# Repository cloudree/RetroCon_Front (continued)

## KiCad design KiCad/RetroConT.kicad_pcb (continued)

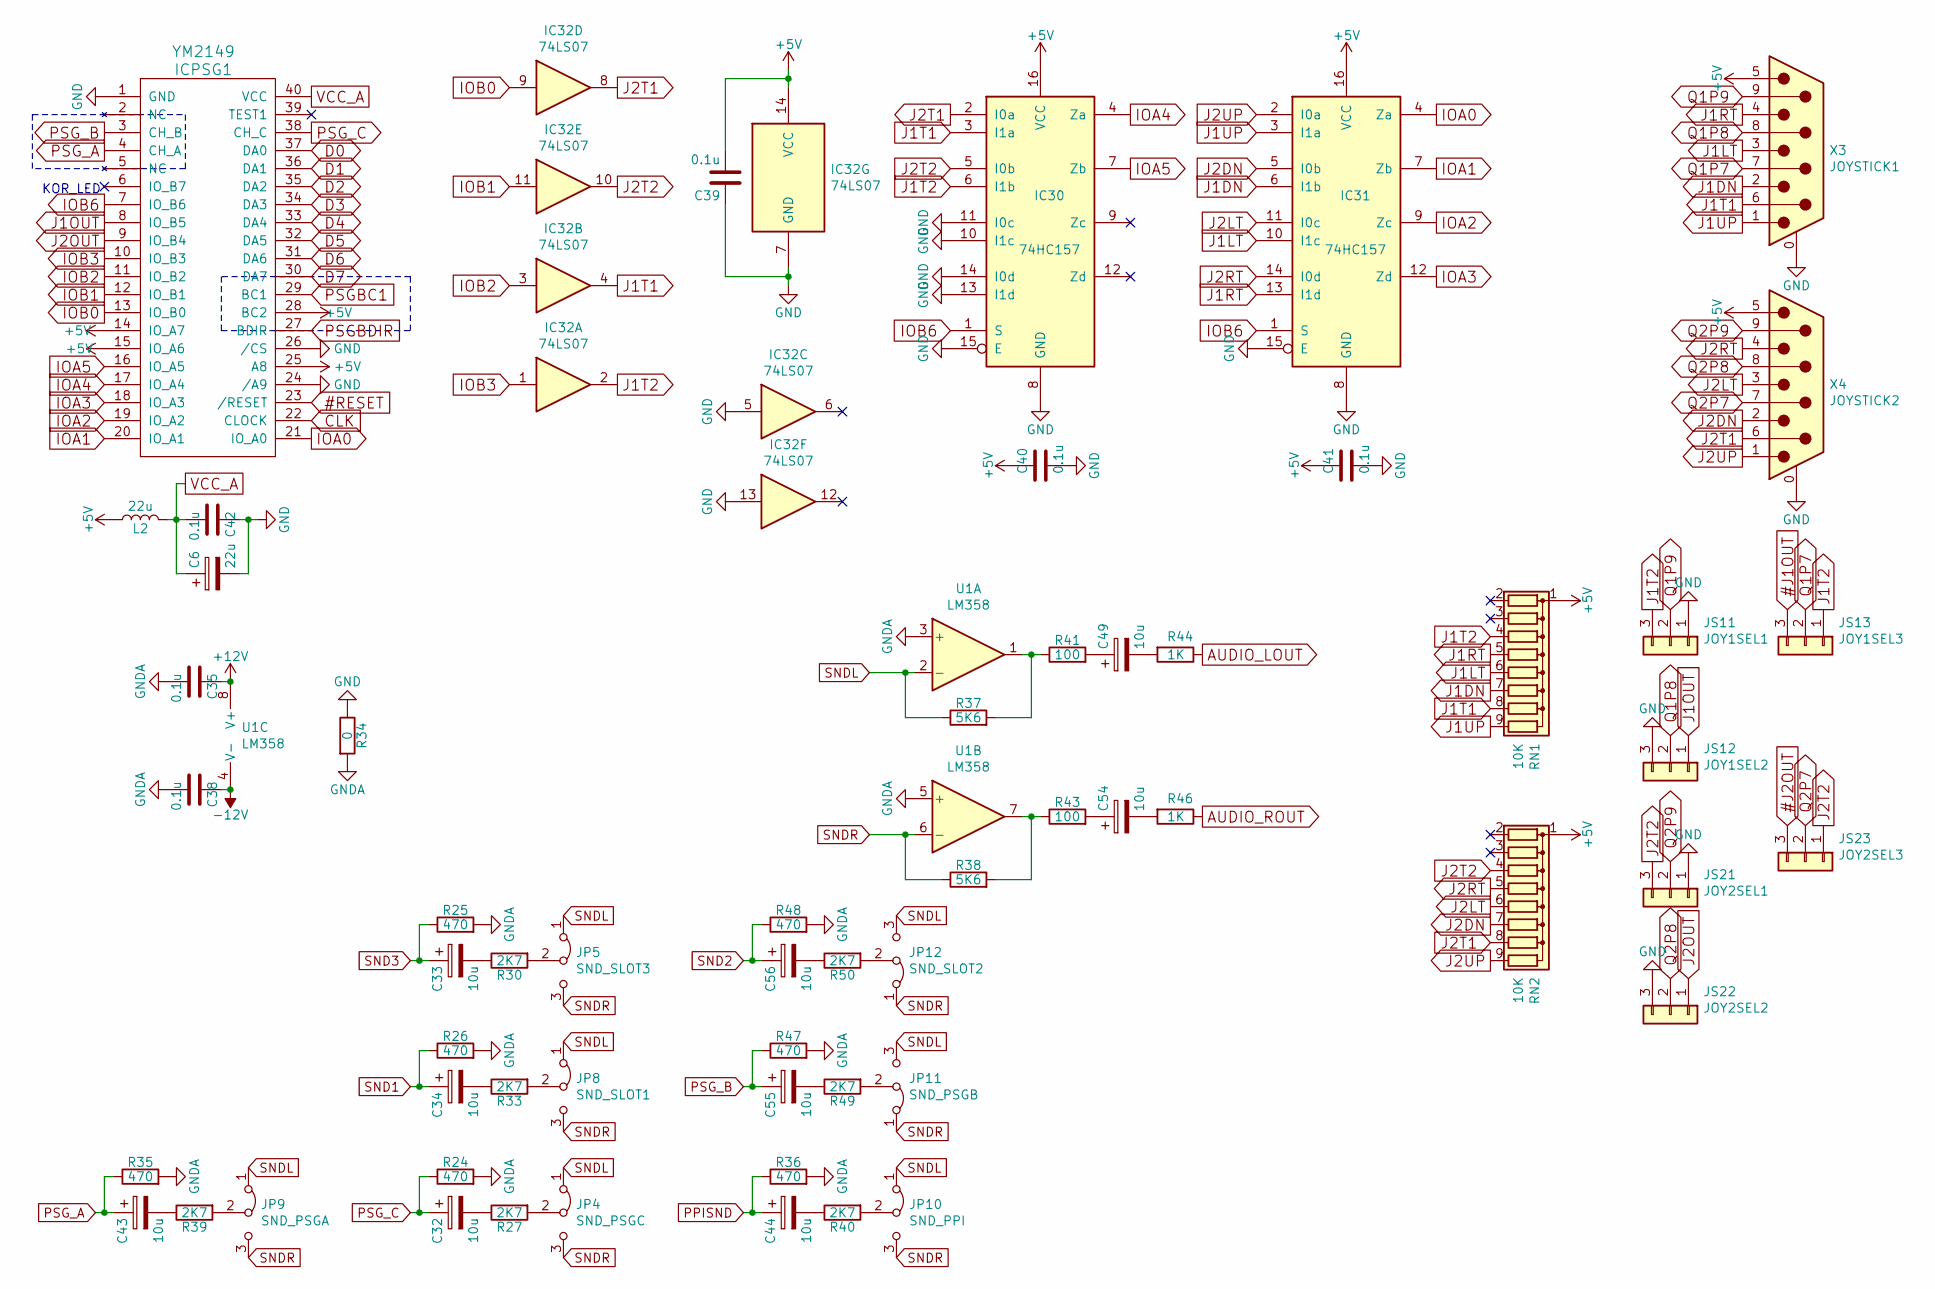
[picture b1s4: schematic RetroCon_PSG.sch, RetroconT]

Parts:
C6: 22u; CP_Radial_D6.3mm_P2.50mm
C32, C33, C34, C43, C44, C49, C54, C55, C56: 10u; CP_Radial_D6.3mm_P2.50mm
C35, C38, C39, C40, C41, C42: 0.1u; C_0805_2012Metric_Pad1.15x1.40mm_HandSolder
IC30, IC31: 74HC157; SOIC-16_3.9x9.9mm_P1.27mm
IC32: 74LS07; SOIC-14_3.9x8.7mm_P1.27mm
ICPSG1: YM2149; DIP-40_W15.24mm_Socket
JP4: SND_PSGC; SolderJumper-3_P1.3mm_Bridged12_RoundedPad1.0x1.5mm_NumberL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
JP5: SND_SLOT3; SolderJumper-3_P1.3mm_Bridged12_RoundedPad1.0x1.5mm_NumberL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
JP8: SND_SLOT1; SolderJumper-3_P1.3mm_Bridged12_RoundedPad1.0x1.5mm_NumberL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
JP9: SND_PSGA; SolderJumper-3_P1.3mm_Bridged12_RoundedPad1.0x1.5mm_NumberL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
JP10: SND_PPI; SolderJumper-3_P1.3mm_Bridged12_RoundedPad1.0x1.5mm_NumberL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
JP11: SND_PSGB; SolderJumper-3_P1.3mm_Bridged12_RoundedPad1.0x1.5mm_NumberL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
JP12: SND_SLOT2; SolderJumper-3_P1.3mm_Bridged12_RoundedPad1.0x1.5mm_NumberL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
JS11: JOY1SEL1; PinSocket_1x03_P2.54mm_Vertical
JS12: JOY1SEL2; PinSocket_1x03_P2.54mm_Vertical
JS13: JOY1SEL3; PinSocket_1x03_P2.54mm_Vertical
JS21: JOY2SEL1; PinSocket_1x03_P2.54mm_Vertical
JS22: JOY2SEL2; PinSocket_1x03_P2.54mm_Vertical
JS23: JOY2SEL3; PinSocket_1x03_P2.54mm_Vertical
L2: 22u; L_0805_2012Metric_Pad1.15x1.40mm_HandSolder
R24, R25, R26, R35, R36, R47, R48: 470; R_0805_HandSoldering
R27, R30, R33, R39, R40, R49, R50: 2K7; R_0805_HandSoldering
R34: 0; R_0805_HandSoldering
R37, R38: 5K6; R_0805_HandSoldering
R41, R43: 100; R_0805_HandSoldering
R44, R46: 1K; R_0805_HandSoldering
RN1, RN2: 10K; R_Array_SIP9
U1: LM358; DIP-8_W7.62mm_Socket
X3: JOYSTICK1; DSUB-9_Male_Horizontal_P2.77x2.84mm_EdgePinOffset4.94mm_Hou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
X4: JOYSTICK2; DSUB-9_Male_Horizontal_P2.77x2.84mm_EdgePinOffset4.94mm_Hou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

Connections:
#ExRESET: ICPSG1.23 (/RESET); also elsewhere on the board
#J1OUT: JS13.3; also elsewhere on the board
#J2OUT: JS23.3; also elsewhere on the board
+5V: C39.2, C40.1, C41.1, IC30.16 (VCC), IC31.16 (VCC), IC32.14 (VCC), ICPSG1.14 (IO_A7), ICPSG1.15 (IO_A6), ICPSG1.25 (A8), ICPSG1.28 (BC2), L2.1, RN1.1 (common), RN2.1 (common), X3.5, X4.5; also elsewhere on the board
+12V: C35.1, U1.8 (V+); also elsewhere on the board
-12V: C38.1, U1.4 (V-); also elsewhere on the board
AUDIO_LOUT: R44.1; also elsewhere on the board
AUDIO_ROUT: R46.1; also elsewhere on the board
CLK: ICPSG1.22 (CLOCK); also elsewhere on the board
D0: ICPSG1.37 (DA0); also elsewhere on the board
D1: ICPSG1.36 (DA1); also elsewhere on the board
D2: ICPSG1.35 (DA2); also elsewhere on the board
D3: ICPSG1.34 (DA3); also elsewhere on the board
D4: ICPSG1.33 (DA4); also elsewhere on the board
D5: ICPSG1.32 (DA5); also elsewhere on the board
D6: ICPSG1.31 (DA6); also elsewhere on the board
D7: ICPSG1.30 (DA7); also elsewhere on the board
GND: C6.2, C39.1, C40.2, C41.2, C42.1, IC30.8 (GND), IC30.10 (I1c), IC30.11 (I0c), IC30.13 (I1d), IC30.14 (I0d), IC30.15 (E), IC31.8 (GND), IC31.15 (E), IC32.5, IC32.7 (GND), IC32.13, ICPSG1.1 (GND), ICPSG1.24 (/A9), ICPSG1.26 (/CS), JS11.1, JS12.3, JS21.1, JS22.3, R34.1, X3.0 (PAD), X4.0 (PAD); also elsewhere on the board
GNDA: C35.2, C38.2, R24.2, R25.2, R26.2, R34.2, R35.2, R36.2, R47.2, R48.2, U1.3 (+), U1.5 (+); also elsewhere on the board
IOA0: IC31.4 (Za), ICPSG1.21 (IO_A0)
IOA1: IC31.7 (Zb), ICPSG1.20 (IO_A1)
IOA2: IC31.9 (Zc), ICPSG1.19 (IO_A2)
IOA3: IC31.12 (Zd), ICPSG1.18 (IO_A3)
IOA4: IC30.4 (Za), ICPSG1.17 (IO_A4)
IOA5: IC30.7 (Zb), ICPSG1.16 (IO_A5)
IOB0: IC32.9, ICPSG1.13 (IO_B0)
IOB1: IC32.11, ICPSG1.12 (IO_B1)
IOB2: IC32.3, ICPSG1.11 (IO_B2)
IOB3: IC32.1, ICPSG1.10 (IO_B3)
IOB6: IC30.1 (S), IC31.1 (S), ICPSG1.7 (IO_B6)
J1DN: IC31.6 (I1b), RN1.7 (R6), X3.2
J1LT: IC31.10 (I1c), RN1.6 (R5), X3.3
J1OUT: ICPSG1.8 (IO_B5), JS12.1; also elsewhere on the board
J1RT: IC31.13 (I1d), RN1.5 (R4), X3.4
J1T1: IC30.3 (I1a), IC32.4, RN1.8 (R7), X3.6
J1T2: IC30.6 (I1b), IC32.2, JS11.3, JS13.1, RN1.4 (R3)
J1UP: IC31.3 (I1a), RN1.9 (R8), X3.1
J2DN: IC31.5 (I0b), RN2.7 (R6), X4.2
J2LT: IC31.11 (I0c), RN2.6 (R5), X4.3
J2OUT: ICPSG1.9 (IO_B4), JS22.1; also elsewhere on the board
J2RT: IC31.14 (I0d), RN2.5 (R4), X4.4
J2T1: IC30.2 (I0a), IC32.8, RN2.8 (R7), X4.6
J2T2: IC30.5 (I0b), IC32.10, JS21.3, JS23.1, RN2.4 (R3)
J2UP: IC31.2 (I0a), RN2.9 (R8), X4.1
unnamed: C32.2, R27.1
unnamed: C33.2, R30.1
unnamed: C34.2, R33.1
unnamed: C43.2, R39.1
unnamed: C44.2, R40.1
unnamed: C49.1, R41.2
unnamed: C49.2, R44.2
unnamed: C54.1, R43.2
unnamed: C54.2, R46.2
unnamed: C55.2, R49.1
unnamed: C56.2, R50.1
unnamed: JP4.2 (C), R27.2
unnamed: JP5.2 (C), R30.2
unnamed: JP8.2 (C), R33.2
unnamed: JP9.2 (C), R39.2
unnamed: JP10.2 (C), R40.2
unnamed: JP11.2 (C), R49.2
unnamed: JP12.2 (C), R50.2
unnamed: R37.2, R41.1, U1.1
unnamed: R38.2, R43.1, U1.7
PPISND: C44.1, R36.1; also elsewhere on the board
PSGBC1: ICPSG1.29 (BC1); also elsewhere on the board
PSGBDIR: ICPSG1.27 (BDIR); also elsewhere on the board
PSG_A: C43.1, ICPSG1.4 (CH_A), R35.1
PSG_B: C55.1, ICPSG1.3 (CH_B), R47.1
PSG_C: C32.1, ICPSG1.38 (CH_C), R24.1
Q1P7: JS13.2, X3.7
Q1P8: JS12.2, X3.8
Q1P9: JS11.2, X3.9
Q2P7: JS23.2, X4.7
Q2P8: JS22.2, X4.8
Q2P9: JS21.2, X4.9
SND1: C34.1, R26.1; also elsewhere on the board
SND2: C56.1, R48.1; also elsewhere on the board
SND3: C33.1, R25.1; also elsewhere on the board
SNDL: JP4.1 (A), JP5.1 (A), JP8.1 (A), JP9.1 (A), JP10.1 (A), JP11.3 (B), JP12.3 (B), R37.1, U1.2 (-)
SNDR: JP4.3 (B), JP5.3 (B), JP8.3 (B), JP9.3 (B), JP10.3 (B), JP11.1 (A), JP12.1 (A), R38.1, U1.6 (-)
VCC_A: C6.1, C42.2, ICPSG1.40 (VCC), L2.2

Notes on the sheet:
KOR_LED

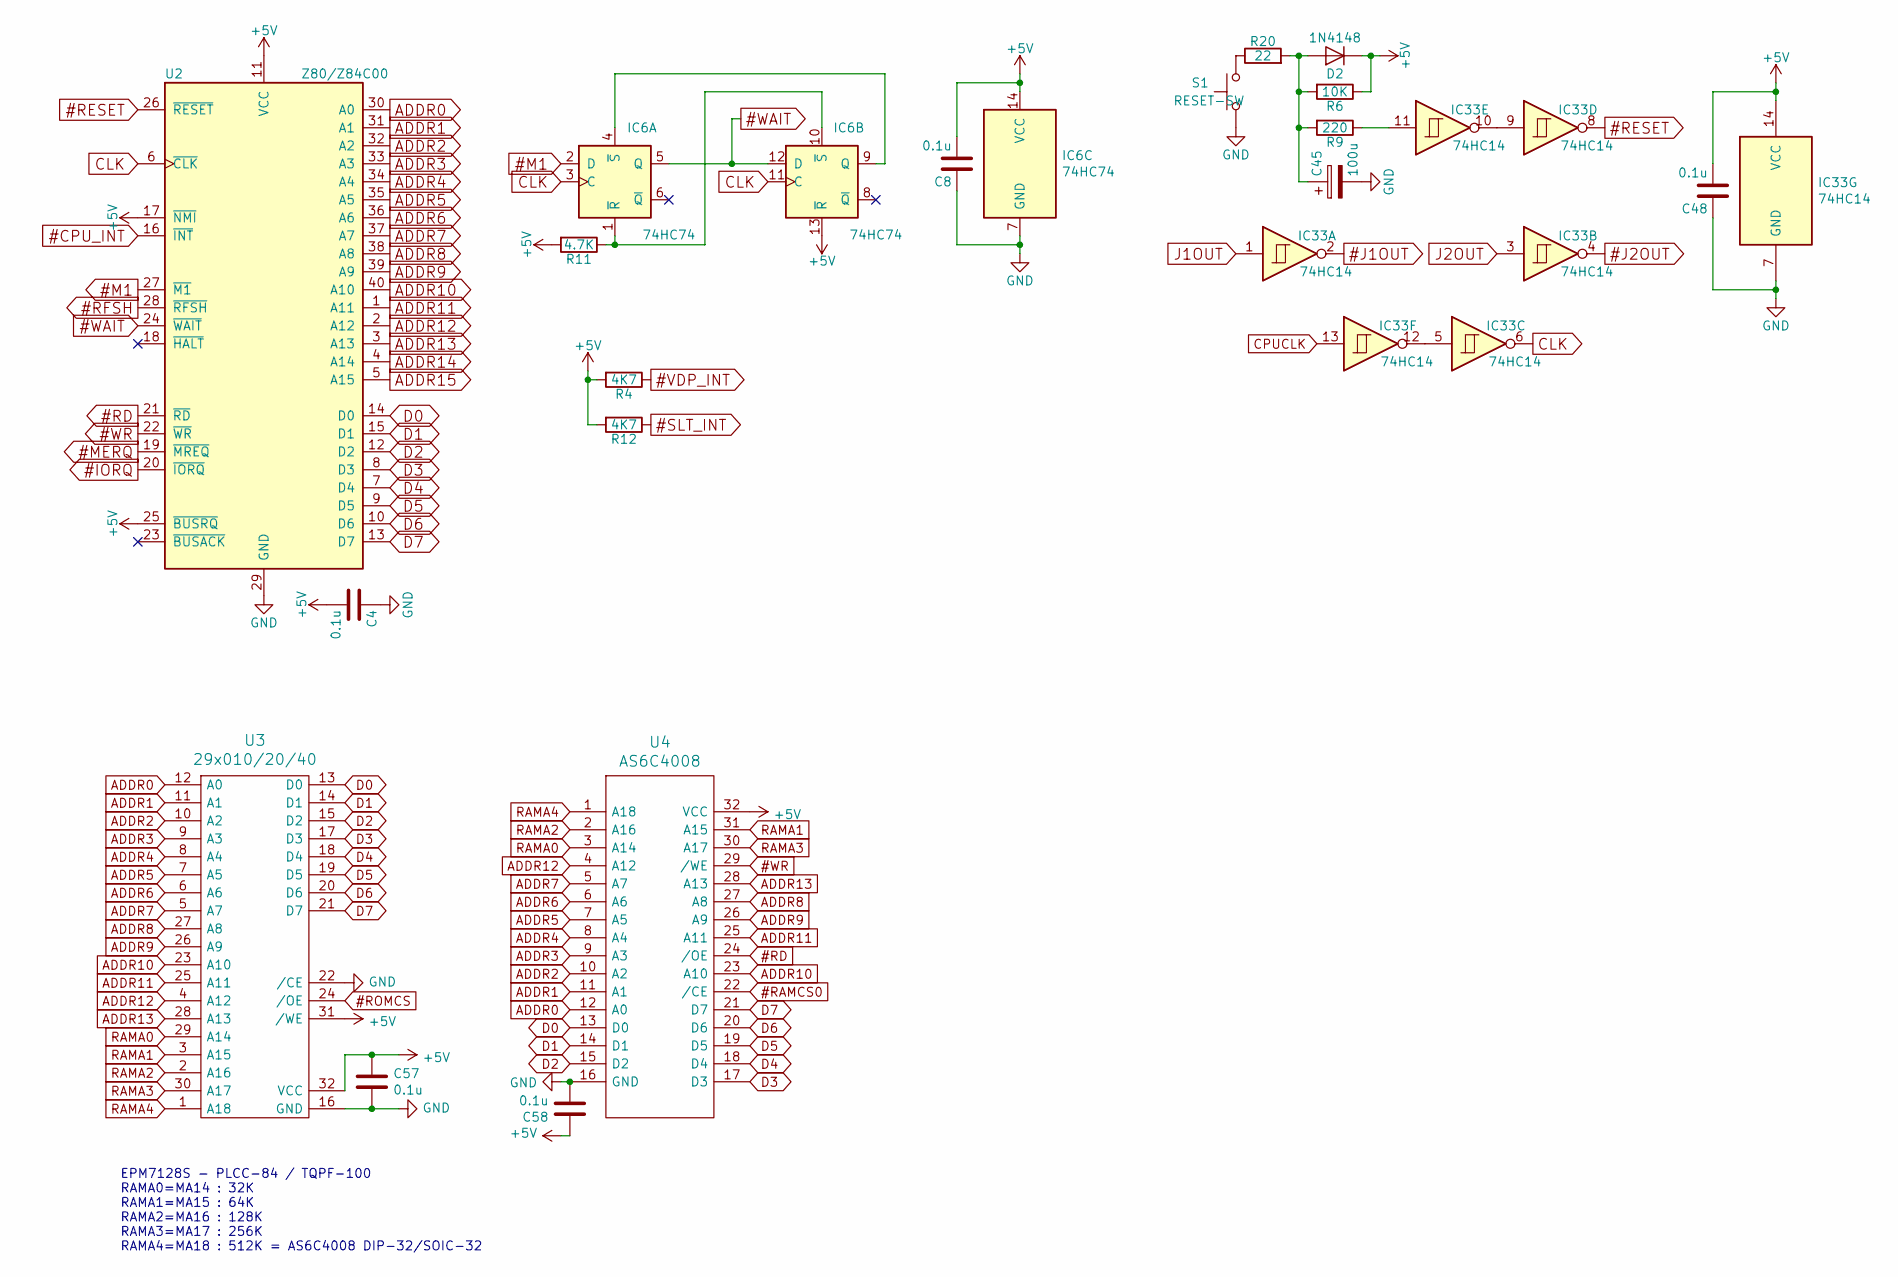
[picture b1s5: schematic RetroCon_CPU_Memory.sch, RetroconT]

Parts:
C4, C8, C48, C57, C58: 0.1u; C_0805_2012Metric_Pad1.15x1.40mm_HandSolder
C45: 100u; CP_Radial_D6.3mm_P2.50mm
D2: 1N4148; D_0805_2012Metric_Pad1.15x1.40mm_HandSolder
IC6: 74HC74; SOIC-14_3.9x8.7mm_P1.27mm
IC33: 74HC14; SOIC-14_3.9x8.7mm_P1.27mm
R4, R12: 4K7; R_0805_HandSoldering
R6: 10K; R_0805_HandSoldering
R9: 220; R_0805_HandSoldering
R11: 4.7K; R_0805_HandSoldering
R20: 22; R_0805_HandSoldering
S1: RESET-SW; Tact_Switch_Long_Angle
U2: Z80/Z84C00; DIP-40_W15.24mm_Socket
U3: 29x010/20/40; DIP-32_W15.24mm_Socket
U4: AS6C4008; DIP-32_W15.24mm_Socket

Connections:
#CPU_INT: U2.16 (~INT~); also elsewhere on the board
#ExIORQ: U2.20 (~IORQ~); also elsewhere on the board
#ExM1: IC6.2 (D), U2.27 (~M1~); also elsewhere on the board
#ExMERQ: U2.19 (~MREQ~); also elsewhere on the board
#ExRD: U2.21 (~RD~), U4.24 (/OE); also elsewhere on the board
#ExRESET: IC33.8, U2.26 (~RESET~); also elsewhere on the board
#ExRFSH: U2.28 (~RFSH~); also elsewhere on the board
#ExWAIT: IC6.5 (Q), IC6.12 (D), U2.24 (~WAIT~); also elsewhere on the board
#ExWR: U2.22 (~WR~), U4.29 (/WE); also elsewhere on the board
#J1OUT: IC33.2; also elsewhere on the board
#J2OUT: IC33.4; also elsewhere on the board
#RAMCS0: U4.22 (/CE); also elsewhere on the board
#ROMCS: U3.24 (/OE); also elsewhere on the board
#SLT_INT: R12.1; also elsewhere on the board
#VDP_INT: R4.1; also elsewhere on the board
+5V: C4.2, C8.2, C48.2, C57.1, C58.1, D2.1 (K), IC6.13 (~R), IC6.14 (VCC), IC33.14 (VCC), R4.2, R6.1, R11.2, R12.2, U2.11 (VCC), U2.17 (~NMI~), U2.25 (~BUSRQ~), U3.31 (/WE), U3.32 (VCC), U4.32 (VCC); also elsewhere on the board
ADDR0: U2.30 (A0), U3.12 (A0), U4.12 (A0); also elsewhere on the board
ADDR1: U2.31 (A1), U3.11 (A1), U4.11 (A1); also elsewhere on the board
ADDR2: U2.32 (A2), U3.10 (A2), U4.10 (A2); also elsewhere on the board
ADDR3: U2.33 (A3), U3.9 (A3), U4.9 (A3); also elsewhere on the board
ADDR4: U2.34 (A4), U3.8 (A4), U4.8 (A4); also elsewhere on the board
ADDR5: U2.35 (A5), U3.7 (A5), U4.7 (A5); also elsewhere on the board
ADDR6: U2.36 (A6), U3.6 (A6), U4.6 (A6); also elsewhere on the board
ADDR7: U2.37 (A7), U3.5 (A7), U4.5 (A7); also elsewhere on the board
ADDR8: U2.38 (A8), U3.27 (A8), U4.27 (A8); also elsewhere on the board
ADDR9: U2.39 (A9), U3.26 (A9), U4.26 (A9); also elsewhere on the board
ADDR10: U2.40 (A10), U3.23 (A10), U4.23 (A10); also elsewhere on the board
ADDR11: U2.1 (A11), U3.25 (A11), U4.25 (A11); also elsewhere on the board
ADDR12: U2.2 (A12), U3.4 (A12), U4.4 (A12); also elsewhere on the board
ADDR13: U2.3 (A13), U3.28 (A13), U4.28 (A13); also elsewhere on the board
ADDR14: U2.4 (A14); also elsewhere on the board
ADDR15: U2.5 (A15); also elsewhere on the board
CLK: IC6.3 (C), IC6.11 (C), IC33.6, U2.6 (~CLK~); also elsewhere on the board
CPUCLK: IC33.13; also elsewhere on the board
D0: U2.14 (D0), U3.13 (D0), U4.13 (D0); also elsewhere on the board
D1: U2.15 (D1), U3.14 (D1), U4.14 (D1); also elsewhere on the board
D2: U2.12 (D2), U3.15 (D2), U4.15 (D2); also elsewhere on the board
D3: U2.8 (D3), U3.17 (D3), U4.17 (D3); also elsewhere on the board
D4: U2.7 (D4), U3.18 (D4), U4.18 (D4); also elsewhere on the board
D5: U2.9 (D5), U3.19 (D5), U4.19 (D5); also elsewhere on the board
D6: U2.10 (D6), U3.20 (D6), U4.20 (D6); also elsewhere on the board
D7: U2.13 (D7), U3.21 (D7), U4.21 (D7); also elsewhere on the board
GND: C4.1, C8.1, C45.2, C48.1, C57.2, C58.2, IC6.7 (GND), IC33.7 (GND), S1.1, U2.29 (GND), U3.16 (GND), U3.22 (/CE), U4.16 (GND); also elsewhere on the board
J1OUT: IC33.1; also elsewhere on the board
J2OUT: IC33.3; also elsewhere on the board
unnamed: C45.1, D2.2 (A), R6.2, R9.2, R20.2
unnamed: IC6.1 (~R), IC6.10 (~S), R11.1
unnamed: IC6.4 (~S), IC6.9 (Q)
unnamed: IC33.9, IC33.10
unnamed: IC33.11, R9.1
unnamed: IC33.5, IC33.12
unnamed: R20.1, S1.2
RAMA0: U3.29 (A14), U4.3 (A14); also elsewhere on the board
RAMA1: U3.3 (A15), U4.31 (A15); also elsewhere on the board
RAMA2: U3.2 (A16), U4.2 (A16); also elsewhere on the board
RAMA3: U3.30 (A17), U4.30 (A17); also elsewhere on the board
RAMA4: U3.1 (A18), U4.1 (A18); also elsewhere on the board

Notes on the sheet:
EPM7128S - PLCC-84 / TQPF-100 RAMA0=MA14 : 32K RAMA1=MA15 : 64K RAMA2=MA16 : 128K RAMA3=MA17 : 256K RAMA4=MA18 : 512K = AS6C4008 DIP-32/SOIC-32

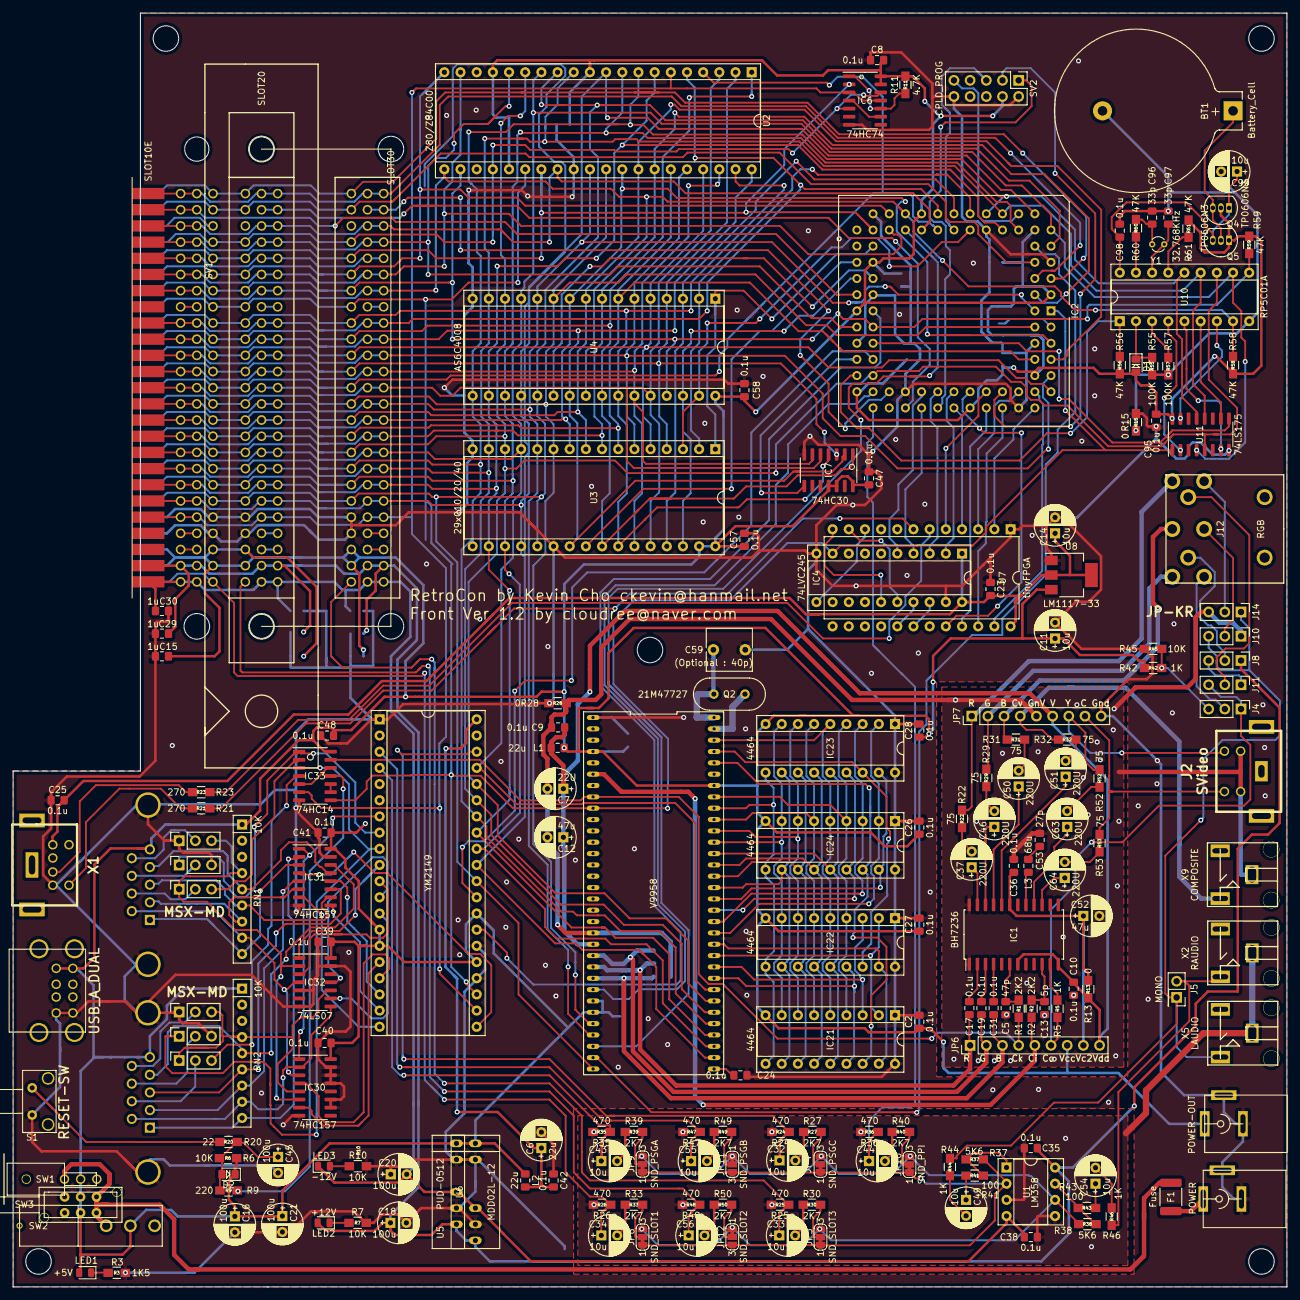
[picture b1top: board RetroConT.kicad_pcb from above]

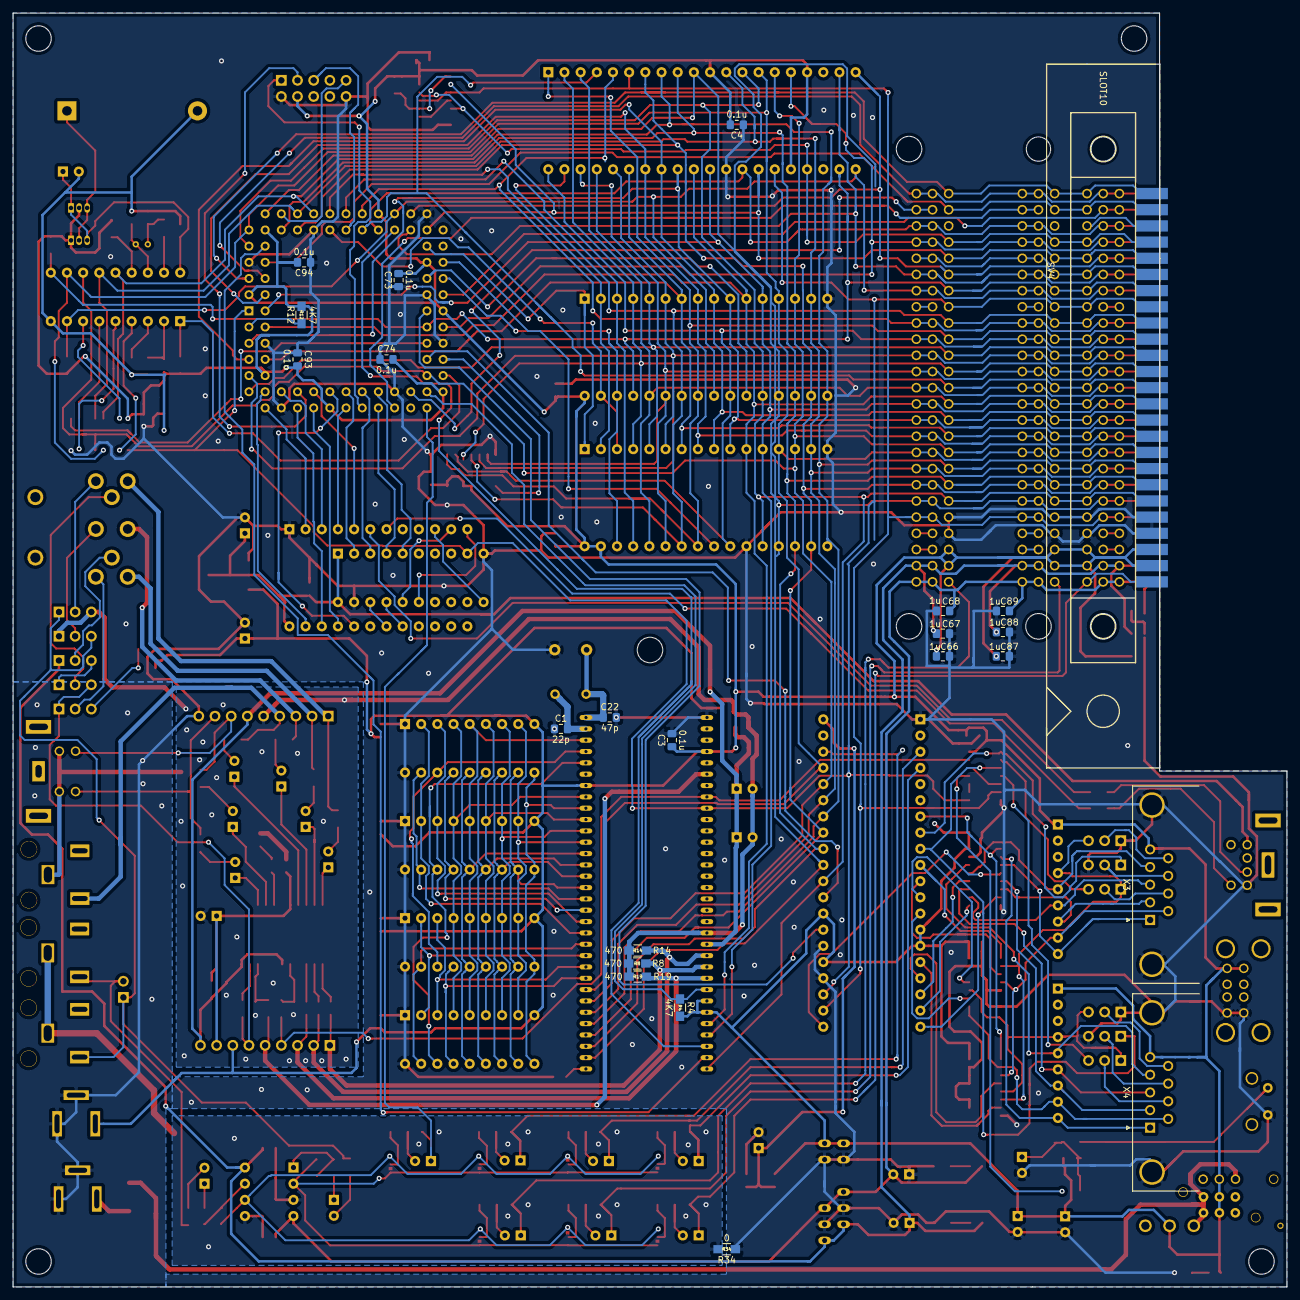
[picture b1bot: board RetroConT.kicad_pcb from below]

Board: 2 copper layers, 200.0 x 200.0 mm, 214 parts (23 on the bottom side), 245 nets.

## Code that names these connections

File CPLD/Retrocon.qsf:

# -------------------------------------------------------------------------- #
#
# Copyright (C) 1991-2013 Altera Corporation
# Your use of Altera Corporation's design tools, logic functions 
# and other software and tools, and its AMPP partner logic 
# functions, and any output files from any of the foregoing 
# (including device programming or simulation files), and any 
# associated documentation or information are expressly subject 
# to the terms and conditions of the Altera Program License 
# Subscription Agreement, Altera MegaCore Function License 
# Agreement, or other applicable license agreement, including, 
# without limitation, that your use is for the sole purpose of 
# programming logic devices manufactured by Altera and sold by 
# Altera or its authorized distributors.  Please refer to the 
# applicable agreement for further details.
#
# -------------------------------------------------------------------------- #
#
# Quartus II 64-Bit
# Version 13.0.1 Build 232 06/12/2013 Service Pack 1 SJ Web Edition
# Date created = 04:59:41  October 24, 2019
#
# -------------------------------------------------------------------------- #
#
# Notes:
#
# 1) The default values for assignments are stored in the file:
#		Retrocon_assignment_defaults.qdf
#    If this file doesn't exist, see file:
#		assignment_defaults.qdf
#
# 2) Altera recommends that you do not modify this file. This
#    file is updated automatically by the Quartus II software
#    and any changes you make may be lost or overwritten.
#
# -------------------------------------------------------------------------- #


set_global_assignment -name FAMILY MAX7000S
set_global_assignment -name DEVICE "EPM7128SLC84-10"
set_global_assignment -name TOP_LEVEL_ENTITY Retrocon
set_global_assignment -name ORIGINAL_QUARTUS_VERSION "13.0 SP1"
set_global_assignment -name PROJECT_CREATION_TIME_DATE "04:59:41  OCTOBER 24, 2019"
set_global_assignment -name LAST_QUARTUS_VERSION "13.0 SP1"
set_global_assignment -name MAX7000_DEVICE_IO_STANDARD TTL
set_global_assignment -name OPTIMIZE_HOLD_TIMING OFF
set_global_assignment -name OPTIMIZE_MULTI_CORNER_TIMING OFF
set_global_assignment -name FITTER_EFFORT "STANDARD FIT"
set_global_assignment -name USE_CONFIGURATION_DEVICE ON
set_global_assignment -name ECO_REGENERATE_REPORT ON
set_global_assignment -name OPTIMIZE_IOC_REGISTER_PLACEMENT_FOR_TIMING "PACK ALL IO REGISTERS"
set_global_assignment -name SLOW_SLEW_RATE OFF
set_global_assignment -name AUTO_TURBO_BIT AUTO
set_location_assignment PIN_67 -to PB[7]
set_location_assignment PIN_68 -to PB[6]
set_location_assignment PIN_70 -to PB[5]
set_location_assignment PIN_76 -to PB[4]
set_location_assignment PIN_69 -to PB[3]
set_location_assignment PIN_64 -to PB[2]
set_location_assignment PIN_73 -to PB[1]
set_location_assignment PIN_74 -to PB[0]
set_location_assignment PIN_56 -to CAPS
set_location_assignment PIN_48 -to CK_RTCAL
set_location_assignment PIN_45 -to CPU_INTb
set_location_assignment PIN_30 -to IORQb
set_location_assignment PIN_34 -to M1b
set_location_assignment PIN_31 -to MREQb
set_location_assignment PIN_9 -to data[7]
set_location_assignment PIN_12 -to data[6]
set_location_assignment PIN_15 -to data[5]
set_location_assignment PIN_17 -to data[4]
set_location_assignment PIN_18 -to data[3]
set_location_assignment PIN_16 -to data[2]
set_location_assignment PIN_52 -to data[1]
set_location_assignment PIN_11 -to data[0]
set_location_assignment PIN_61 -to keyMAT[3]
set_location_assignment PIN_60 -to keyMAT[2]
set_location_assignment PIN_63 -to keyMAT[1]
set_location_assignment PIN_65 -to keyMAT[0]
set_location_assignment PIN_24 -to addrH[15]
set_location_assignment PIN_25 -to addrH[14]
set_location_assignment PIN_75 -to addrL[7]
set_location_assignment PIN_77 -to addrL[6]
set_location_assignment PIN_80 -to addrL[5]
set_location_assignment PIN_4 -to addrL[4]
set_location_assignment PIN_79 -to addrL[3]
set_location_assignment PIN_81 -to addrL[2]
set_location_assignment PIN_84 -to addrL[1]
set_location_assignment PIN_2 -to addrL[0]
set_location_assignment PIN_21 -to RAMA[1]
set_location_assignment PIN_22 -to RAMA[0]
set_location_assignment PIN_51 -to RTCCSb
set_location_assignment PIN_46 -to WRb
set_location_assignment PIN_49 -to addr13_8b
set_location_assignment PIN_28 -to RDb
set_location_assignment PIN_37 -to ROM_OEb
set_location_assignment PIN_1 -to RSTb
set_location_assignment PIN_83 -to SLT_INTb
set_location_assignment PIN_58 -to SLTbo[2]
set_location_assignment PIN_41 -to SLTbo[1]
set_location_assignment PIN_54 -to SPK
set_location_assignment PIN_5 -to PG1RDb
set_location_assignment PIN_6 -to PG2RDb
set_location_assignment PIN_8 -to PG12RDb
set_location_assignment PIN_50 -to PSGBC1
set_location_assignment PIN_44 -to PSGBDIR
set_location_assignment PIN_27 -to RFSHb
set_location_assignment PIN_10 -to VDP_CSRb
set_location_assignment PIN_29 -to VDP_CSWb
set_location_assignment PIN_55 -to VDP_INTb
set_location_assignment PIN_20 -to RAMA[2]
set_location_assignment PIN_40 -to RAM_CSb
set_location_assignment PIN_39 -to RAMA[3]
set_location_assignment PIN_57 -to RAMA[4]
set_global_assignment -name VERILOG_FILE ramMapper.v
set_global_assignment -name VERILOG_FILE PPI8255.v
set_global_assignment -name VERILOG_FILE slotExp.v
set_global_assignment -name VERILOG_FILE Retrocon.v
set_global_assignment -name VERILOG_FILE PPI8255_SLT.v
set_global_assignment -name CDF_FILE Retrocon.cdf

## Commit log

2020-04-04 Fix up some bugs
    fix up around XTAL and add variable capacitor.
    fix the position of Joystick ports.
    fix +5V supply around DC2DC.
2020-04-04 fix up some details
    change proper value of Capacitor for XTAL
